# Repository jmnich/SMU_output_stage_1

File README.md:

# SMU_output_stage_1

Output stage module for HtBlog Source Measure Unit

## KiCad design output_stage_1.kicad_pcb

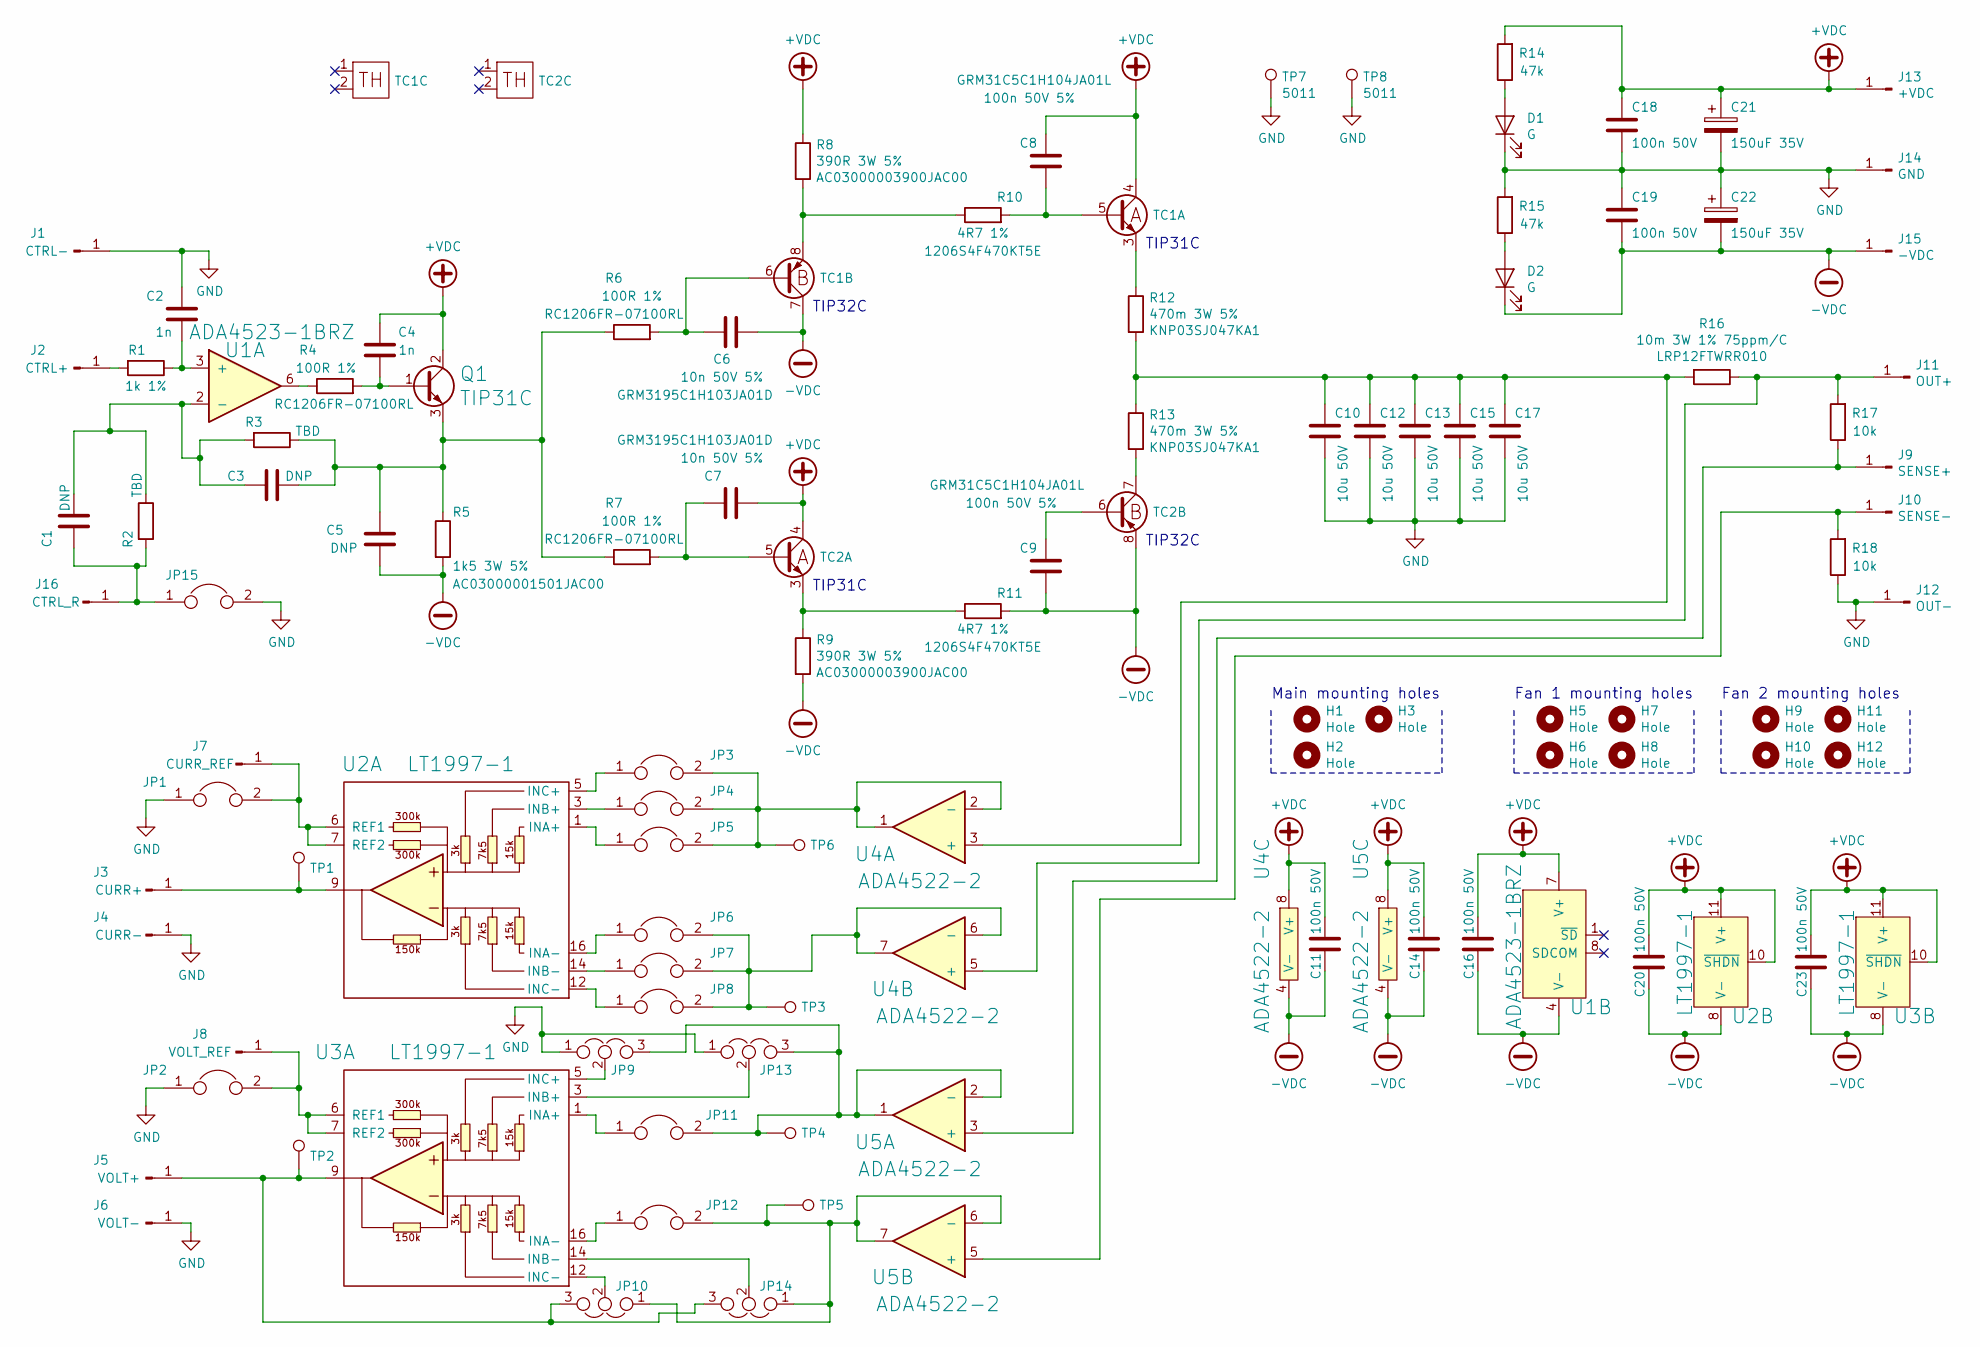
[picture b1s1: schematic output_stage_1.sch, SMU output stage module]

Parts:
C1, C3, C5: DNP; C_0603_1608Metric_Pad1.05x0.95mm_HandSolder
C2, C4: 1n; C_0603_1608Metric_Pad1.05x0.95mm_HandSolder
C6, C7: 10n 50V 5%; C_1206_3216Metric_Pad1.42x1.75mm_HandSolder; MPN GRM3195C1H103JA01D
C8, C9: 100n 50V 5%; C_1206_3216Metric_Pad1.42x1.75mm_HandSolder; MPN GRM31C5C1H104JA01L
C10, C12, C13, C15, C17: 10u 50V; C_1206_3216Metric_Pad1.42x1.75mm_HandSolder; MPN CL31B106KBHNNNE
C11, C14, C16, C18, C19, C20, C23: 100n 50V; C_0603_1608Metric_Pad1.05x0.95mm_HandSolder
C21, C22: 150uF 35V; C_Radial_D10.0mm_H12.5mm_P5.00mm; MPN 870055675010
D1, D2: G; LED_0603_1608Metric_Pad1.05x0.95mm_HandSolder
H1, H2, H3, H5, H6, H7, H8, H9, H10, H11, H12: Hole; MountingHole_3.2mm_M3
J1: CTRL-; MountingHole_2.7mm_Pad_Via
J2: CTRL+; MountingHole_2.7mm_Pad_Via
J3: CURR+; MountingHole_2.7mm_Pad_Via
J4: CURR-; MountingHole_2.7mm_Pad_Via
J5: VOLT+; MountingHole_2.7mm_Pad_Via
J6: VOLT-; MountingHole_2.7mm_Pad_Via
J7: CURR_REF; MountingHole_2.7mm_Pad_Via
J8: VOLT_REF; MountingHole_2.7mm_Pad_Via
J9: SENSE+; MountingHole_2.7mm_Pad_Via
J10: SENSE-; MountingHole_2.7mm_Pad_Via
J11: OUT+; MountingHole_2.7mm_Pad_Via
J12: OUT-; MountingHole_2.7mm_Pad_Via
J13: +VDC; MountingHole_2.7mm_Pad_Via
J14: GND; MountingHole_2.7mm_Pad_Via
J15: -VDC; MountingHole_2.7mm_Pad_Via
J16: CTRL_R; MountingHole_2.7mm_Pad_Via
JP1, JP2, JP3, JP4, JP5, JP6, JP7, JP8, JP11, JP12, JP15: Jumper; SolderJumper-2_P1.3mm_Open_RoundedPad1.0x1.5mm
JP9, JP10, JP13, JP14: Jumper_NC_Dual; SolderJumper-3_P1.3mm_Open_RoundedPad1.0x1.5mm
Q1: TIP31C; TO-220-3_Horizontal_TabDown
R1: 1k 1%; R_0603_1608Metric_Pad1.05x0.95mm_HandSolder
R2, R3: TBD; R_0603_1608Metric_Pad1.05x0.95mm_HandSolder
R4, R6, R7: 100R 1%; R_1206_3216Metric_Pad1.42x1.75mm_HandSolder; MPN RC1206FR-07100RL
R5: 1k5 3W 5%; R_Axial_DIN0516_L15.5mm_D5.0mm_P20.32mm_Horizontal; MPN AC03000001501JAC00
R8, R9: 390R 3W 5%; R_Axial_DIN0516_L15.5mm_D5.0mm_P20.32mm_Horizontal; MPN AC03000003900JAC00
R10, R11: 4R7 1%; R_1206_3216Metric_Pad1.42x1.75mm_HandSolder; MPN 1206S4F470KT5E
R12, R13: 470m 3W 5%; R_Axial_DIN0617_L17.0mm_D6.0mm_P20.32mm_Horizontal; MPN KNP03SJ047KA1
R14, R15: 47k; R_0603_1608Metric_Pad1.05x0.95mm_HandSolder
R16: 10m 3W 1% 75ppm/C; R_2512_6332Metric_Pad1.52x3.35mm_HandSolder; MPN LRP12FTWRR010
R17, R18: 10k; R_0603_1608Metric_Pad1.05x0.95mm_HandSolder
TC1, TC2: power_couple_type1; power_couple_radiator1
TP1, TP2, TP3, TP4, TP5, TP6: TestPoint; TestPoint_Pad_D2.0mm
TP7, TP8: 5011; TestPoint_Keystone_5010-5014_Multipurpose
U1: ADA4523-1BRZ; SOIC-8_3.9x4.9mm_P1.27mm
U2, U3: LT1997-1; LT1997-1_MSOP_package
U4, U5: ADA4522-2; MSOP-8_3x3mm_P0.65mm

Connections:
+VDC: C4.1, C7.2, C8.2, C11.1, C14.1, C16.1, C18.1, C20.1, C21.1, C23.1, J13.1, Q1.2 (C), R8.1, R14.2, TC1.4 (C), TC2.4 (C), U1.7 (V+), U2.10 (~SHDN), U2.11 (V+), U3.10 (~SHDN), U3.11 (V+), U4.8 (V+), U5.8 (V+)
-VDC: C5.2, C6.2, C9.1, C11.2, C14.2, C16.2, C19.2, C20.2, C22.2, C23.2, D2.1 (K), J15.1, R5.2, R9.2, R11.2, TC1.7 (C), TC2.8 (E), U1.4 (V-), U2.8 (V-), U3.8 (V-), U4.4 (V-), U5.4 (V-)
GND: C2.1, C10.1, C12.1, C13.1, C15.1, C17.1, C18.2, C19.1, C21.2, C22.1, D1.1 (K), J1.1, J4.1, J6.1, J12.1, J14.1, JP1.1, JP2.1, JP9.1, JP13.1, JP15.2, R15.2, R18.1, TP7.1, TP8.1
unnamed: C1.1, C3.2, R2.1, R3.2, U1.2 (-)
unnamed: C1.2, J16.1, JP15.1, R2.2
unnamed: C2.2, R1.1, U1.3 (+)
unnamed: C3.1, C5.1, Q1.3 (E), R3.1, R5.1, R6.1, R7.1
unnamed: C4.2, Q1.1 (B), R4.2
unnamed: C6.1, R6.2, TC1.6 (B)
unnamed: C7.1, R7.2, TC2.5 (B)
unnamed: C8.1, R10.2, TC1.5 (B)
unnamed: C9.2, TC2.6 (B)
unnamed: C10.2, C12.2, C13.2, C15.2, C17.2, R12.2, R13.1, R16.2, U4.3 (+)
unnamed: D1.2 (A), R14.1
unnamed: D2.2 (A), R15.1
unnamed: J2.1, R1.2
unnamed: J3.1, TP1.1, U2.9
unnamed: J5.1, JP10.3, JP14.3, TP2.1, U3.9
unnamed: J7.1, JP1.2, U2.6 (REF1), U2.7 (REF2)
unnamed: J8.1, JP2.2, U3.6 (REF1), U3.7 (REF2)
unnamed: J9.1, R17.1, U5.3 (+)
unnamed: J10.1, R18.2, U5.5 (+)
unnamed: J11.1, R16.1, R17.2, U4.5 (+)
unnamed: JP3.1, U2.5 (INC+)
unnamed: JP3.2, JP4.2, JP5.2, TP6.1, U4.1, U4.2 (-)
unnamed: JP4.1, U2.3 (INB+)
unnamed: JP5.1, U2.1 (INA+)
unnamed: JP6.1, U2.16 (INA-)
unnamed: JP6.2, JP7.2, JP8.2, TP3.1, U4.6 (-), U4.7
unnamed: JP7.1, U2.14 (INB-)
unnamed: JP8.1, U2.12 (INC-)
unnamed: JP9.2, U3.5 (INC+)
unnamed: JP10.1, JP12.2, JP14.1, TP5.1, U5.6 (-), U5.7
unnamed: JP10.2, U3.12 (INC-)
unnamed: JP11.1, U3.1 (INA+)
unnamed: JP9.3, JP11.2, JP13.3, TP4.1, U5.1, U5.2 (-)
unnamed: JP12.1, U3.16 (INA-)
unnamed: JP13.2, U3.3 (INB+)
unnamed: JP14.2, U3.14 (INB-)
unnamed: R4.1, U1.6
unnamed: R8.2, R10.1, TC1.8 (E)
unnamed: R9.1, R11.1, TC2.3 (E)
unnamed: R12.1, TC1.3 (E)
unnamed: R13.2, TC2.7 (C)

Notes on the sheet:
TIP32C
TIP31C
Main mounting holes
Fan 1 mounting holes
Fan 2 mounting holes

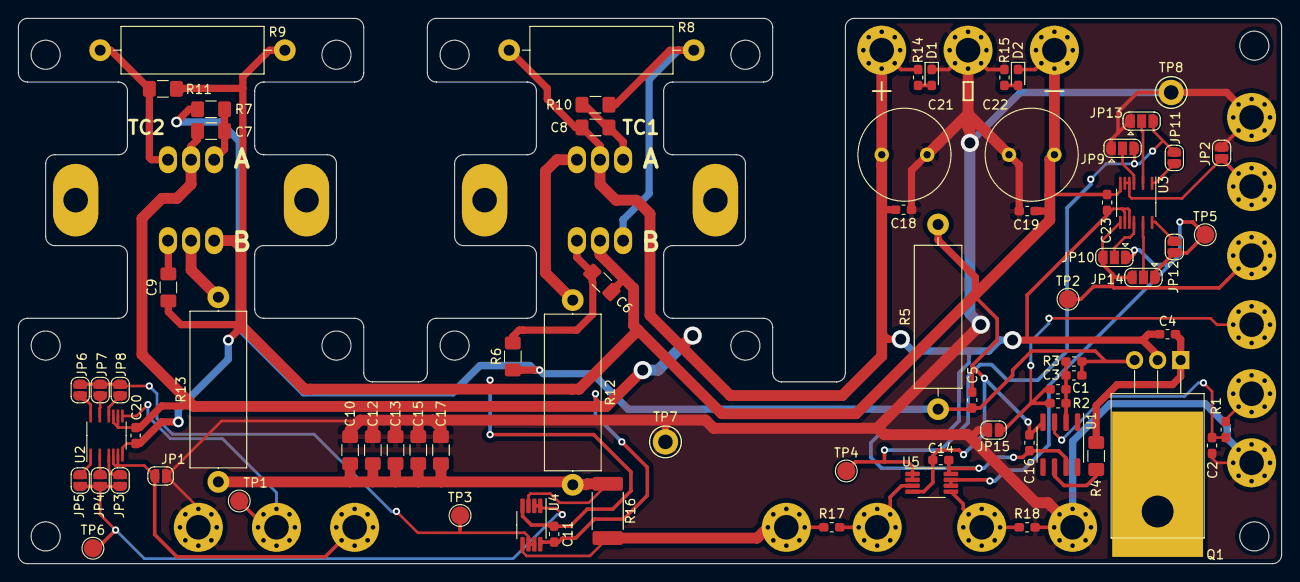
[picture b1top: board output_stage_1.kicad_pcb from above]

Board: 2 copper layers, 139.0 x 60.0 mm, 101 parts (0 on the bottom side), 44 nets.

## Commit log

2020-10-17 Add image
2020-10-17 readme fix
2020-10-27 production files
